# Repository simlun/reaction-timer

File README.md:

Reaction Timer
==============

A complete product based on Experiment 18 of [Make Electronics by Charles Platt][makeelec] - the Reaction Timer.

My Modifications
----------------

* A real PCB design based on Platt's circuit diagrams and breadboarded version.
* Instead of `IC4`, the 3-in-1 package Platt is using, I'm using 3 separate 7-segment LED display modules (`IC4a-c`).
* I'm using a 5.6 kOhm `R12` as the current limiting resistor for the LED instead of Platt's 1 kOhms.
* There are two `R10`'s in the circuit diagram on [page 178][makeelec]. The one that is connected to `IC7` will be called `R13` here.

Bill Of Materials
-----------------

* Case: Hammond Manufacturing 1591CTCL clear polycarbonate box
* Power: 9 V battery connector cable
* `D1`: Reverse voltage protection 1N4004 diode

* `IC1`, `IC2`, `IC3`: DIP-16 4026 decade counters with 7-segment display driver
* `IC4a`, `IC4b`, `IC4c`: 7-segment 14 mm common cathode LED display
* `IC5`, `IC6`, `IC7`: DIP-8 555 timers

* `LED1`: Red LED

* `S2`, `S3`, `S4`: Normally open push buttons

* `C1`: 100 uF capacitor
* `C2`, `C3`, `C4`, `C6`: 0.1 uF capacitor
* `C5`: 10 uF capacitor

* `R1`, `R2`, `R3`, `R4`, `R5`, `R6`: 1 kOhm LED display current limiting resistors
* `R7`: 1 kOhm resistor for calibrating the clock timer (`IC5`)
* `R8`: 10 kOhm trimmer potentiometer for calibrating the clock timer (`IC5`)
* `R9`, `R10`, `R13`: 1 kOhm pull-up resistors
* `R14`: 1 kOhm pull-down resistor
* `R11`: 330 kOhm resistor for calibrating the delay timer (`IC7`)
* `R12`: 5.6 kOhm resistor

[makeelec]: http://www.amazon.com/Make-Electronics-Discovery-Charles-Platt/dp/0596153740

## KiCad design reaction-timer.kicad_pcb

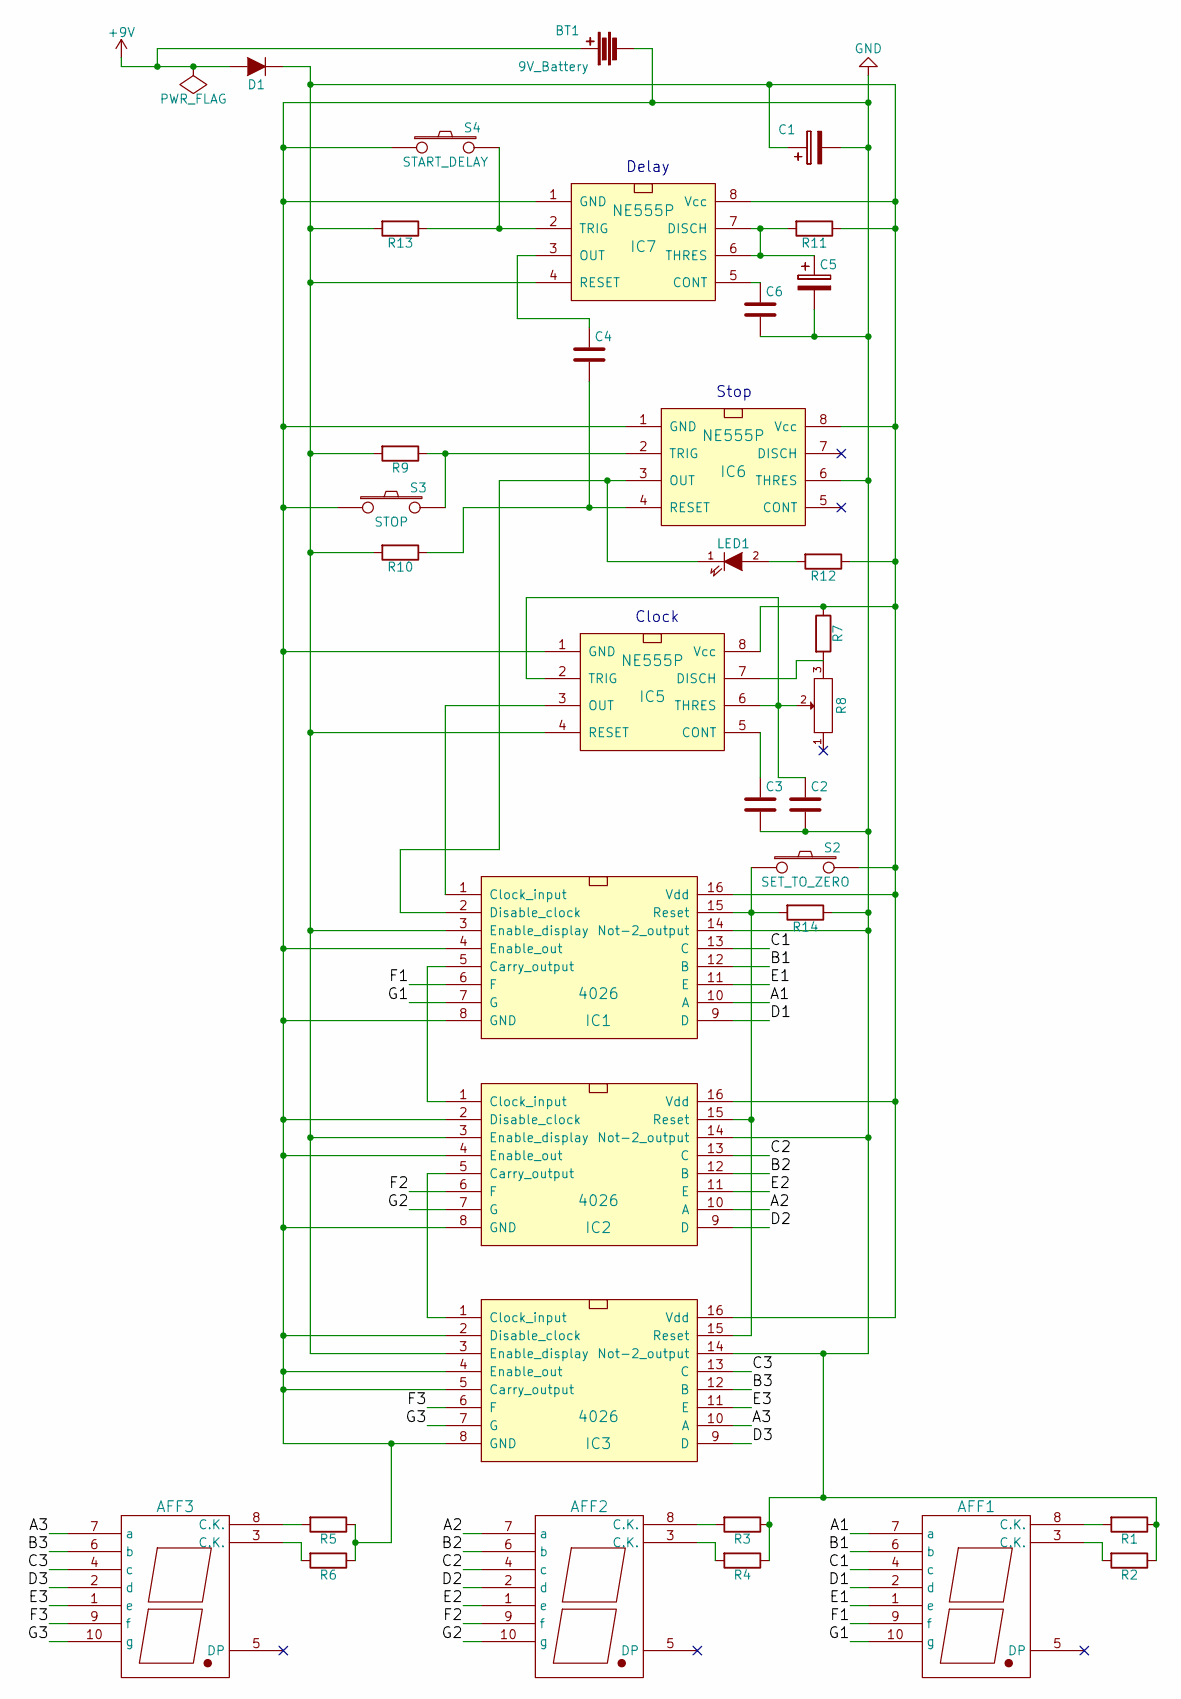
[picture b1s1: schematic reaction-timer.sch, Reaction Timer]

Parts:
AFF1, AFF2, AFF3: LTS-6980HR; 7SegmentLED_LTS6760_LTS6780
BT1: 9V_Battery; Pin_Header_Straight_1x02
C1: CP; Elko_vert_11x5mm_RM2.5
C2, C3, C4, C6: C; C_Disc_D7.5_P5
C5: CP; Elko_vert_11x5mm_RM2
D1: D; Diode_DO-41_SOD81_Horizontal_RM10
IC1, IC2, IC3: 4026; DIP-16_W7.62mm_LongPads
IC5, IC6, IC7: NE555P; DIP-8_W7.62mm_LongPads
LED1: LED; LED-5MM
R1, R2, R3, R4, R5, R6, R7, R9, R10, R11, R12, R13, R14: R; Resistor_Horizontal_RM10mm
R8: POT; Potentiometer_Bourns_3296W_3-8Zoll_Inline_ScrewUp
S2: SET_TO_ZERO; Pin_Header_Straight_1x02
S3: STOP; Pin_Header_Straight_1x02
S4: START_DELAY; Pin_Header_Straight_1x02

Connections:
+9V: BT1.1, D1.2 (A)
/A1: AFF1.7 (a), IC1.10 (A)
/A2: AFF2.7 (a), IC2.10 (A)
/A3: AFF3.7 (a), IC3.10 (A)
/B1: AFF1.6 (b), IC1.12 (B)
/B2: AFF2.6 (b), IC2.12 (B)
/B3: AFF3.6 (b), IC3.12 (B)
/C1: AFF1.4 (c), IC1.13 (C)
/C2: AFF2.4 (c), IC2.13 (C)
/C3: AFF3.4 (c), IC3.13 (C)
/D1: AFF1.2 (d), IC1.9 (D)
/D2: AFF2.2 (d), IC2.9 (D)
/D3: AFF3.2 (d), IC3.9 (D)
/E1: AFF1.1 (e), IC1.11 (E)
/E2: AFF2.1 (e), IC2.11 (E)
/E3: AFF3.1 (e), IC3.11 (E)
/F1: AFF1.9 (f), IC1.6 (F)
/F2: AFF2.9 (f), IC2.6 (F)
/F3: AFF3.9 (f), IC3.6 (F)
/G1: AFF1.10 (g), IC1.7 (G)
/G2: AFF2.10 (g), IC2.7 (G)
/G3: AFF3.10 (g), IC3.7 (G)
GND: BT1.2, C1.2, C2.2, C3.2, C5.2, C6.2, IC1.4 (Enable_out), IC1.8 (GND), IC1.14 (Not-2_output), IC2.2 (Disable_clock), IC2.4 (Enable_out), IC2.8 (GND), IC2.14 (Not-2_output), IC3.2 (Disable_clock), IC3.4 (Enable_out), IC3.5 (Carry_output), IC3.8 (GND), IC3.14 (Not-2_output), IC5.1 (GND), IC6.1 (GND), IC6.6 (THRES), IC7.1 (GND), R1.1, R2.1, R3.1, R4.1, R5.1, R6.1, R14.1, S3.1, S4.1
unnamed: AFF1.3 (C.K.), R2.2
unnamed: AFF1.8 (C.K.), R1.2
unnamed: AFF2.3 (C.K.), R4.2
unnamed: AFF2.8 (C.K.), R3.2
unnamed: AFF3.3 (C.K.), R6.2
unnamed: AFF3.8 (C.K.), R5.2
unnamed: C1.1, D1.1 (K), IC1.3 (Enable_display), IC1.16 (Vdd), IC2.3 (Enable_display), IC2.16 (Vdd), IC3.3 (Enable_display), IC3.16 (Vdd), IC5.4 (RESET), IC5.8 (Vcc), IC6.8 (Vcc), IC7.4 (RESET), IC7.8 (Vcc), R7.1, R9.2, R10.2, R11.1, R12.1, R13.2, S2.2
unnamed: C2.1, IC5.2 (TRIG), IC5.6 (THRES), R8.2
unnamed: C3.1, IC5.5 (CONT)
unnamed: C4.1, IC7.3 (OUT)
unnamed: C4.2, IC6.4 (RESET), R10.1
unnamed: C5.1, IC7.6 (THRES), IC7.7 (DISCH), R11.2
unnamed: C6.1, IC7.5 (CONT)
unnamed: IC1.1 (Clock_input), IC5.3 (OUT)
unnamed: IC1.2 (Disable_clock), IC6.3 (OUT), LED1.1 (K)
unnamed: IC1.5 (Carry_output), IC2.1 (Clock_input)
unnamed: IC1.15 (Reset), IC2.15 (Reset), IC3.15 (Reset), R14.2, S2.1
unnamed: IC2.5 (Carry_output), IC3.1 (Clock_input)
unnamed: IC5.7 (DISCH), R7.2, R8.3
unnamed: IC6.2 (TRIG), R9.1, S3.2
unnamed: IC7.2 (TRIG), R13.1, S4.2
unnamed: LED1.2 (A), R12.2

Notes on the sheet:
Delay
Stop
Clock

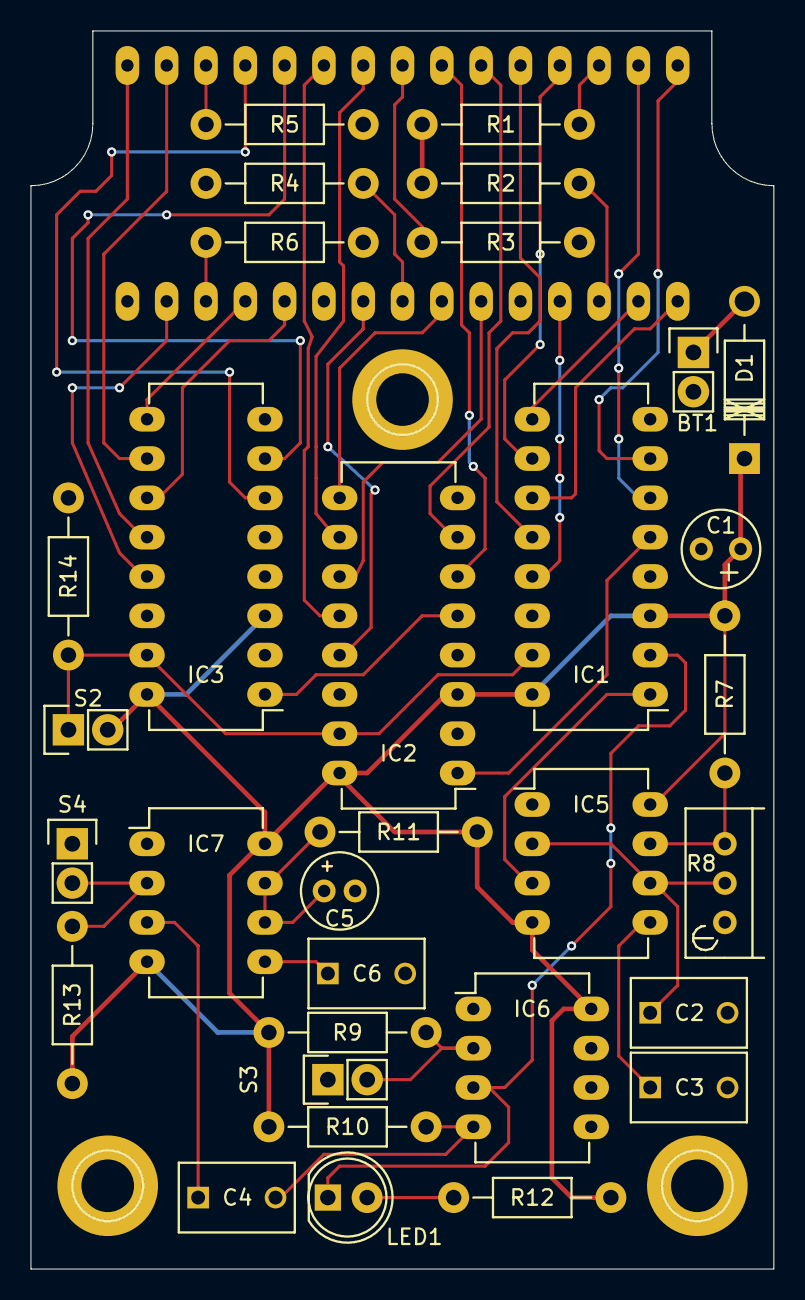
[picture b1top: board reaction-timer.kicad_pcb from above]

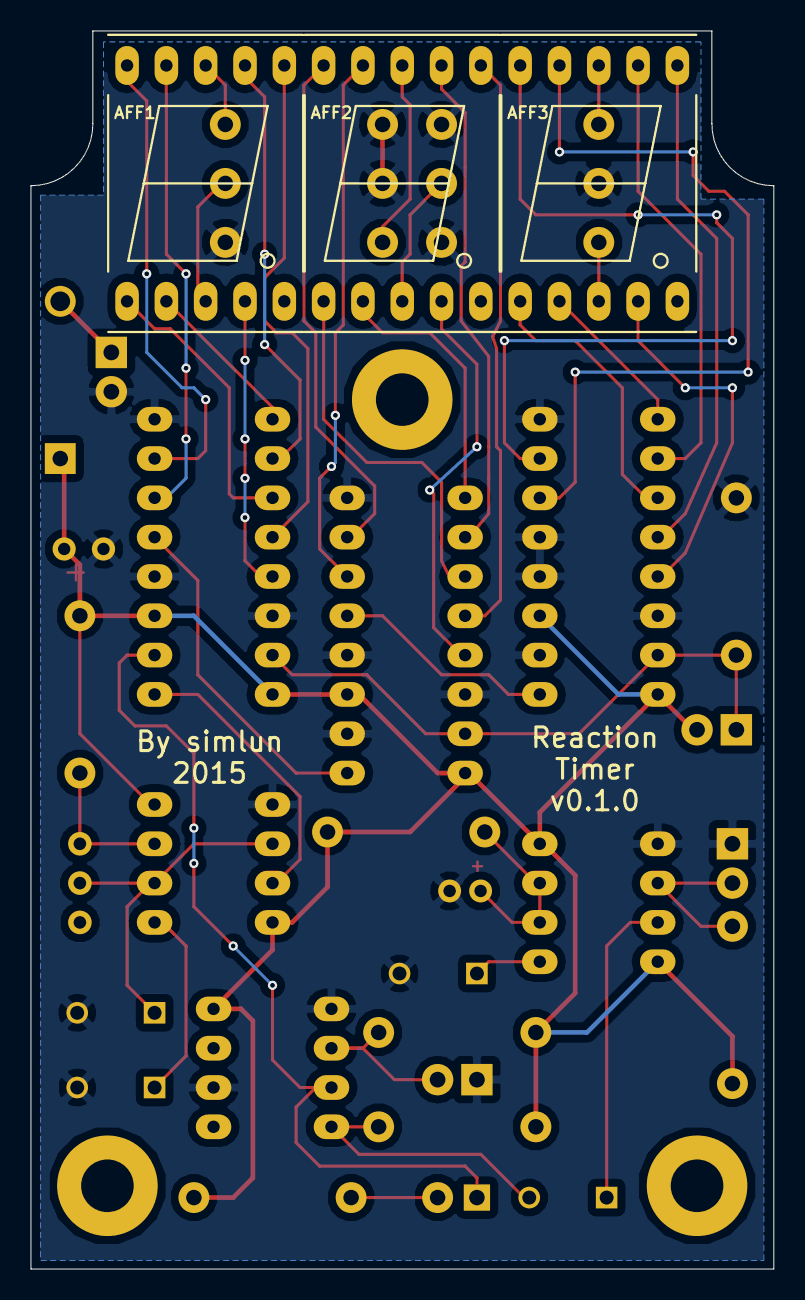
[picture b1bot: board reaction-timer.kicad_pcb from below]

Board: 2 copper layers, 48.0 x 80.0 mm, 35 parts (3 on the bottom side), 45 nets.

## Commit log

2015-06-07 Add initial readme and empty KiCad project
2015-06-07 Add empty PCB layout
2015-06-07 Add 48x80 mm board edges
2015-06-07 Add some data sheets
2015-06-07 Add the control section of the schematic
2015-06-07 Add 4026 decade counters to schematic
2015-06-07 Add 7-segment displays
2015-06-07 Add connections to most significant digit display
2015-06-08 Connect all 7-seg displays to driver chips
2015-06-08 Fix bugs in connection labeling
2015-06-08 Add reverse voltage protection diode
2015-06-08 Add schematic rendered as PDF
2015-06-09 Generate netlist
2015-06-09 Associate displays, capacitors and diode to footprints
2015-06-09 Associate all footprints
2015-06-09 Associate last footprints and add battery
2015-06-09 Change button footprints to pin header instead of wire pad
2015-06-09 Read netlist
2015-06-09 Start placing footprints on board
2015-06-11 Add mounting holes to PCB
2015-06-11 Start connecting some ICs on the PCB to see if it's feasible
2015-06-13 Connect all display pins of IC3
2015-06-21 Place and connect IC2
2015-06-21 Place and connect IC1
    - Now all 7-seg displays are connected
2015-06-21 Place and connect S2 and R14
2015-06-21 Place and connect IC5
2015-06-21 Place and connect IC6
2015-06-21 Place IC7
2015-06-21 Connect IC7
2015-06-21 Move IC1 wiring
2015-06-21 Add +9V to the Power net class
2015-06-21 Connect +9V to filter cap C1
2015-06-21 Move power input
2015-06-22 Connect Vcc to the 7-seg display, but notice a problem!
    - I've connected the displays as common anode, not common cathode (as
    they should be).
2015-06-22 Fix 7-seg common anode/cathode schematic confusion
2015-06-22 Generate new netlist
2015-06-22 Fix PCB according to new netlist
2015-06-22 Connect Vcc everywhere
2015-06-22 Ground fill
2015-06-22 Move components to improve ground fill
2015-06-22 Move bottom layer trace to improve ground fill
2015-06-22 Adjust silkscreen text font size and placement
2015-06-22 Add silk screen text
2015-06-22 Plot Gerber files and drill file
2015-06-22 Finalize and package version 0.1.0
2015-06-22 Add 3D renders to README
2015-07-11 Bugfix: IC6 pin 6 should be GND not VCC
2015-07-11 Add new bugfixed schematic
